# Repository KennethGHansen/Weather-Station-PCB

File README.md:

## Weather Station PCB
I will be making a simple PCB in KICAD which can hold the ESP32, display and Bosch weather sensor in pin holder rows for easy mounting and reuse of components 

STATUS 08-05-2026
PCB done and order sent to JLCPCB. Status there right now is that production is complete, so only shipping remains.

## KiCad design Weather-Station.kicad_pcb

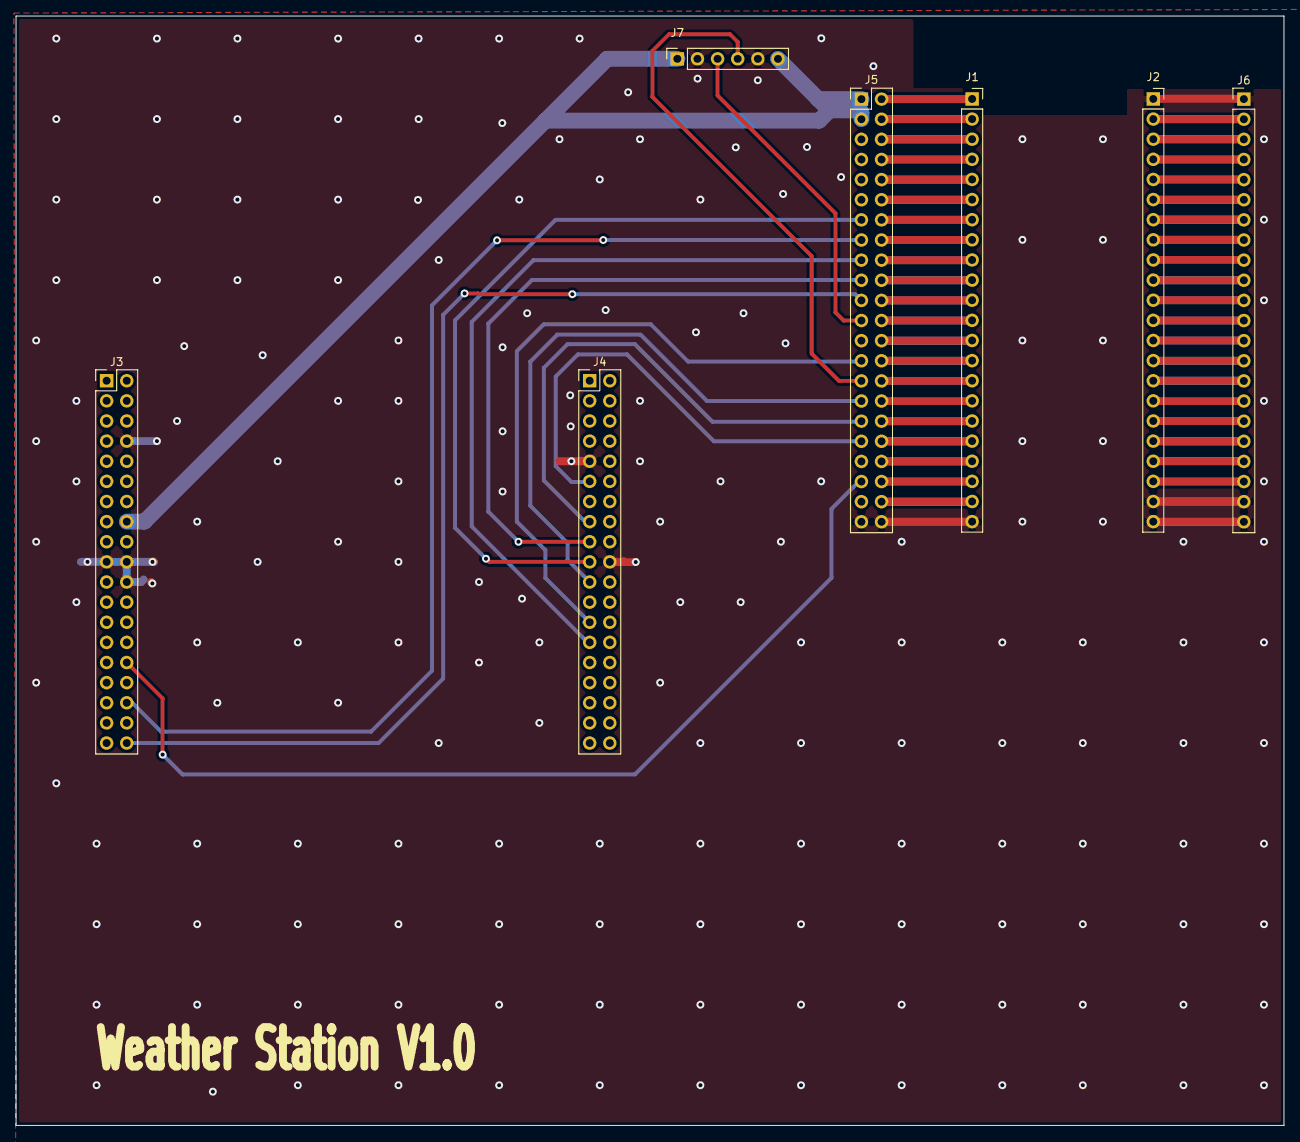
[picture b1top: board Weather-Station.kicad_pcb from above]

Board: 2 copper layers, 160.0 x 140.0 mm, 7 parts (0 on the bottom side), 54 nets.

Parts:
J1, J2: Conn_01x22; PinSocket_1x22_P2.54mm_Vertical
J3: CN2; PinHeader_2x19_P2.54mm_Vertical
J4: CN3; PinHeader_2x19_P2.54mm_Vertical
J5: Conn_02x22_Odd_Even; PinHeader_2x22_P2.54mm_Vertical
J6: Conn_01x22; PinHeader_1x22_P2.54mm_Vertical
J7: Conn_01x06; PinSocket_1x06_P2.54mm_Vertical

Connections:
+3.3V: J3.16, J5.1, J5.3, J7.1, J7.6
/BME_SCL: J5.29, J7.4
/BME_SDA: J5.23, J7.3
/CENTER: J4.19, J5.13
/DISP_CS: J4.21, J5.31
/DISP_DC: J4.25, J5.27
/DISP_MOSI: J4.15, J5.33
/DISP_RESET: J3.30, J5.39
/DISP_SCLK: J4.11, J5.35
/DOWN: J4.27, J5.17
/LEFT: J4.17, J5.19
/RIGHT: J3.34, J5.15
/UP: J3.38, J5.21
GND: J1.22, J2.1, J2.21, J2.22, J3.8, J3.19, J3.20, J3.22, J4.9, J4.20, J5.43, J5.44, J6.1, J6.21, J6.22, J7.2, J7.5
unnamed: J1.1, J5.2
unnamed: J1.2, J5.4
unnamed: J1.3, J5.6
unnamed: J1.4, J5.8
unnamed: J1.5, J5.10
unnamed: J1.6, J5.12
unnamed: J1.7, J5.14
unnamed: J1.8, J5.16
unnamed: J1.9, J5.18
unnamed: J1.10, J5.20
unnamed: J1.11, J5.22
unnamed: J1.12, J5.24
unnamed: J1.13, J5.26
unnamed: J1.14, J5.28
unnamed: J1.15, J5.30
unnamed: J1.16, J5.32
unnamed: J1.17, J5.34
unnamed: J1.18, J5.36
unnamed: J1.19, J5.38
unnamed: J1.20, J5.40
unnamed: J1.21, J5.42
unnamed: J2.2, J6.2
unnamed: J2.3, J6.3
unnamed: J2.4, J6.4
unnamed: J2.5, J6.5
unnamed: J2.6, J6.6
unnamed: J2.7, J6.7
unnamed: J2.8, J6.8
unnamed: J2.9, J6.9
unnamed: J2.10, J6.10
unnamed: J2.11, J6.11
unnamed: J2.12, J6.12
unnamed: J2.13, J6.13
unnamed: J2.14, J6.14
unnamed: J2.15, J6.15
unnamed: J2.16, J6.16
unnamed: J2.17, J6.17
unnamed: J2.18, J6.18
unnamed: J2.19, J6.19
unnamed: J2.20, J6.20

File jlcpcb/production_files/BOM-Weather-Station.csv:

Comment,Designator,Footprint,LCSC,Quantity
CN2,J3,PinHeader_2x19_P2.54mm_Vertical,C7430415,1
CN3,J4,PinHeader_2x19_P2.54mm_Vertical,C7430415,1
Conn_01x06,J7,PinSocket_1x06_P2.54mm_Vertical,C5224026,1
Conn_01x22,"J1,J2",PinSocket_1x22_P2.54mm_Vertical,C53200741,2
Conn_01x22,J6,PinHeader_1x22_P2.54mm_Vertical,C7430378,1
Conn_02x22_Odd_Even,J5,PinHeader_2x22_P2.54mm_Vertical,C22465945,1

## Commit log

2026-05-03 WIP: Finding pin headers/rows
2026-05-03 WIP: Adding display and ESP32
2026-05-04 WIP: Finding components on jlcpcb and merging
2026-05-04 WIP: Started routing
2026-05-05 WIP: Routing started
2026-05-05 Routing done
2026-05-08 PCB done
